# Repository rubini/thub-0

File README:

This is the "two hour uC board".  I designed it for a conference,
held on 2015-11 in Bozen.

The PCB can plug in a breadboard: the two power pins and the I/O strip
are there to that aim.

It as a atmega/attiny board (i.e. the arduino CPU).  You can fit
attiny48, atmega8, atmega88, atmega168 and atmega328.
If you mount the xtal you can program the fuses for 16MHz operation,
otherwise 8MHz.

Peripherals are:
   - 3 rgb leds
   - one button
   - one output led (on a pwm pin)
   - uext connector (uart, i2c, spi)
   - pin strip for analog
   - pin strip for other I/O pins

There is video of my talk, but I find myself quite boring. Moreover,
the screen is not visible in the video:
   https://www.sfscon.it/it/workshop/open-hardware-6/

After producing 50 and leaving 10 of them to conference attendees, I'm
now using the boards for other stuff, like teaching soldering (where
attendees can keep on device.

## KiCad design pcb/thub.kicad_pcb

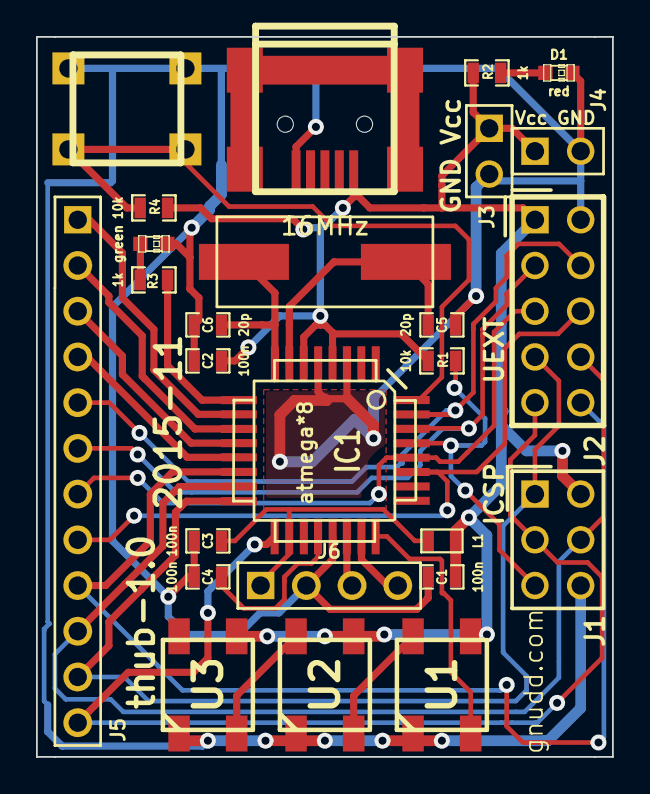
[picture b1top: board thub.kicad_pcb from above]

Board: 2 copper layers, 32.0 x 40.0 mm, 26 parts (0 on the bottom side), 29 nets.

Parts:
C1, C2, C3, C4: 100n; SM0603_Capa
C5, C6: 20p; SM0603_Capa
CON1: USB-MINI-B; USB_MINI_B
D1: red; LED-0603
D2: green; LED-0603
IC1: atmega*8; TQFP32
J1: ICSP; pin_array_3x2
J2: UEXT; PIN_ARRAY_5x2
J3: millefori; PIN_ARRAY_2X1
J4: breadboard; PIN_ARRAY_2X1
J5: STRIP-12
J6: STRIP-4
L1: 10uH; SM0603
R1, R4: 10k; SM0603_Resistor
R2, R3: 1k; SM0603_Resistor
SW1: BUTTON; SW
U1, U2, U3: WS2812B
X1: 16MHz; Xtal-smd

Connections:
/ADC0: IC1.23, J6.4
/ADC7: IC1.22, J6.3
/AREF: C4.1, IC1.20
/BUTTON: IC1.32, R4.1, SW1.3, SW1.4
/LEDPWM: IC1.9, R3.1
/MISO: IC1.16, J1.1, J2.7, J5.11
/MOSI: IC1.15, J1.4, J2.8, J5.10
/Neopixel: IC1.24, U1.4
/PB0: IC1.12, J5.3
/PB1: IC1.13, J5.4
/PD6: IC1.10, J5.1
/PD7: IC1.11, J5.2
/RESET: IC1.29, J1.5, R1.2
/RXD: IC1.31, J2.4, J5.5
/SCK: IC1.17, J1.3, J2.9, J5.12
/SCL: IC1.28, J2.5, J5.7
/SDA: IC1.27, J2.6, J5.8
/SSEL: IC1.14, J2.10, J5.9
/TXD: IC1.30, J2.3, J5.6
/X1: C5.1, IC1.7, X1.1
/X2: C6.1, IC1.8, X1.2
GND: C1.2, C2.2, C3.2, C4.2, C5.2, C6.2, CON1.5, D1.2, D2.2, IC1.3, IC1.5, IC1.21, J1.6, J2.2, J3.2, J4.2, J6.2, SW1.1, SW1.2, U1.3, U2.3, U3.3
GNDPWR: CON1.6, CON1.7, CON1.8, CON1.9
unnamed: U1.2, U2.4
unnamed: U2.2, U3.4
unnamed: D2.1, R3.2
unnamed: D1.1, R2.2
VAA: C3.1, IC1.18, J6.1, L1.2
VCC: C1.1, C2.1, CON1.1, IC1.4, IC1.6, J1.2, J2.1, J3.1, J4.1, L1.1, R1.1, R2.1, R4.2, U1.1, U2.1, U3.1

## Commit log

2015-11-03 initial version, too many libs
2015-11-12 sw: copied Makefile from leder
2015-11-12 pcb: final minor details
2015-11-12 pcb/output: what I printed in 50 instances
2015-11-12 sw: added library files, changed Makefile, added empty.c
2015-11-12 gitignore stuff
2015-11-12 lib: saved all thub components to thub.lib (for eeschema)
2015-11-13 sw: added io.c
2015-11-13 sw/empty: toggle led
2015-11-13 sw: added tick1s.c
2015-11-13 sw: added neopixel, almost working
2015-11-13 sw: fix neopixel init
2015-11-13 sw: added sema.c
2015-11-13 lib: added stuff to thub.mod
2017-05-16 added trivial README
